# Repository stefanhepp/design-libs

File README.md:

README
------

Collection of design files and templates for 3D modelling and PCB design.

- `boards`: Contains various PCB boards and schematics
- `kicad`: KiCAD symbols, footprints and templates (for design rules)

KiCAD Libraries
---------------

### Symbols

The `kicad/symbols` folder contains the following symbol libraries:
- `Custom_Symbols`: A library of various schematic symbols.
    - `R_Pack04_SIL`: A copy of the KiCAD `R_Pack04` symbol, but using throughhole SIL package footprint and pin numbering, since the standard KiCAD SIL symbols use too much space.
    - `Mini-DIN-2x6`: Two mini-DIN 6pin units in one symbol, to use with a dual-miniDIN-6 socket
- `Custom_MCU_Module': A library of MCU devkit symbols.
    - `ESP32-DevKitC_fixed`: A copy of the Expressif ESP32 38pin devkit symbol, but using alternative footprints.
    - `ESP32-WROOM32-Devkit`: Symbol for the 30pin ESP32 dev boards.

### Footprints and 3D Models

The `kicad/footprints` folder contains the following footprint libraries:
- `Custom_Heatsinks.pretty`: A footprint library for various heatsinks.
    - `Heatsink_Aavid_TO-220_H12.7mm`: Simple TO220 heatsink
- `Custom_Connectors.pretty`: A footprint library for various connectors.
- `Custom_Module.pretty`: A footprint library for various MCU devkit modules.

The `kicad/3dmodels` folder contains the following 3D models, used with the footprints:
- `Custom_Connectors.3dmodels`: 3D models of connectors
    - `DIN5 PCB DELTRON`: DIN-5 PCB Socket, model from https://grabcad.com/library/din5-pcb-socket-90

### Board Templates

The `kicad/templates` folder contains PCB setting templates:
- Single-sided PCB, 0.3mm track width (fine tracks, allows routing between pins)
- Single-sided PCB, 0.4mm track width (coarse tracks, easy to mill)
- Double-sided PCB, 0.3mm track width (fine tracks, allows routing between pins)
- Double-sided PCB, 0.4mm track width (coarse tracks, easy to mill)

Additional Libraries, ...
-------------------------

### KiCAD Libraries

- Teensy Symbols, footprints, 3D models
    - https://github.com/XenGi/teensy_library
    - https://github.com/XenGi/teensy.pretty
- Arduino Symbols, footprints, 3D models
    - https://github.com/g200kg/kicad-lib-arduino.git

### Board Templates

- Aisler PCB template:
- PCBWay PCB template:

License
-------
Shield: [![CC BY-SA 4.0][cc-by-sa-shield]][cc-by-sa]

This work is licensed under a
[Creative Commons Attribution-ShareAlike 4.0 International License][cc-by-sa].

[![CC BY-SA 4.0][cc-by-sa-image]][cc-by-sa]

[cc-by-sa]: http://creativecommons.org/licenses/by-sa/4.0/
[cc-by-sa-image]: https://licensebuttons.net/l/by-sa/4.0/88x31.png
[cc-by-sa-shield]: https://img.shields.io/badge/License-CC%20BY--SA%204.0-lightgrey.svg

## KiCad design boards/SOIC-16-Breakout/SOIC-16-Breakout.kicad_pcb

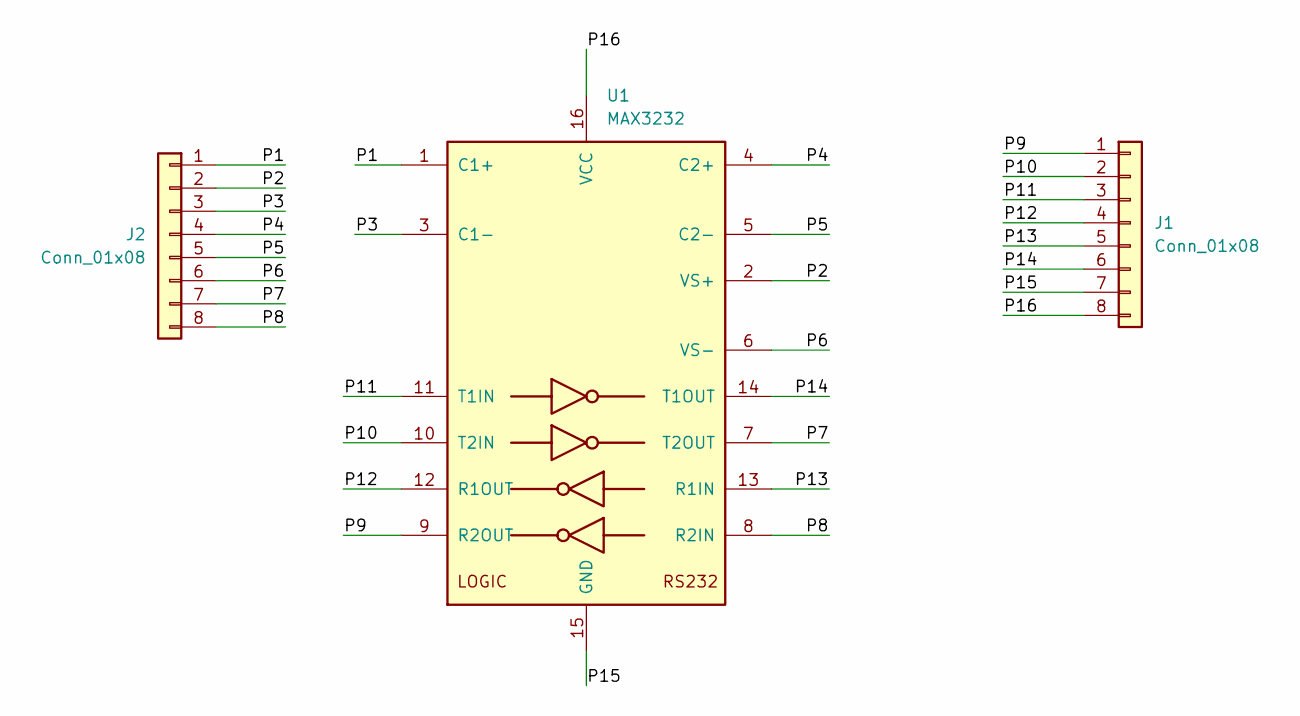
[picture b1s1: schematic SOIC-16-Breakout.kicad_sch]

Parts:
J1, J2: Conn_01x08; PinHeader_1x08_P2.54mm_Vertical
U1: MAX3232; SOIC-16_3.9x9.9mm_P1.27mm

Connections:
/P1: J2.1, U1.1 (C1+)
/P2: J2.2, U1.2 (VS+)
/P3: J2.3, U1.3 (C1-)
/P4: J2.4, U1.4 (C2+)
/P5: J2.5, U1.5 (C2-)
/P6: J2.6, U1.6 (VS-)
/P7: J2.7, U1.7 (T2OUT)
/P8: J2.8, U1.8 (R2IN)
/P9: J1.1, U1.9 (R2OUT)
/P10: J1.2, U1.10 (T2IN)
/P11: J1.3, U1.11 (T1IN)
/P12: J1.4, U1.12 (R1OUT)
/P13: J1.5, U1.13 (R1IN)
/P14: J1.6, U1.14 (T1OUT)
/P15: J1.7, U1.15 (GND)
/P16: J1.8, U1.16 (VCC)

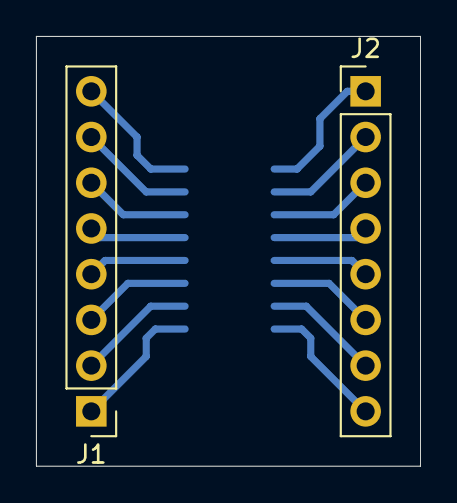
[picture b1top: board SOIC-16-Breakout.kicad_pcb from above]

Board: 2 copper layers, 21.3 x 23.9 mm, 3 parts (1 on the bottom side), 16 nets.

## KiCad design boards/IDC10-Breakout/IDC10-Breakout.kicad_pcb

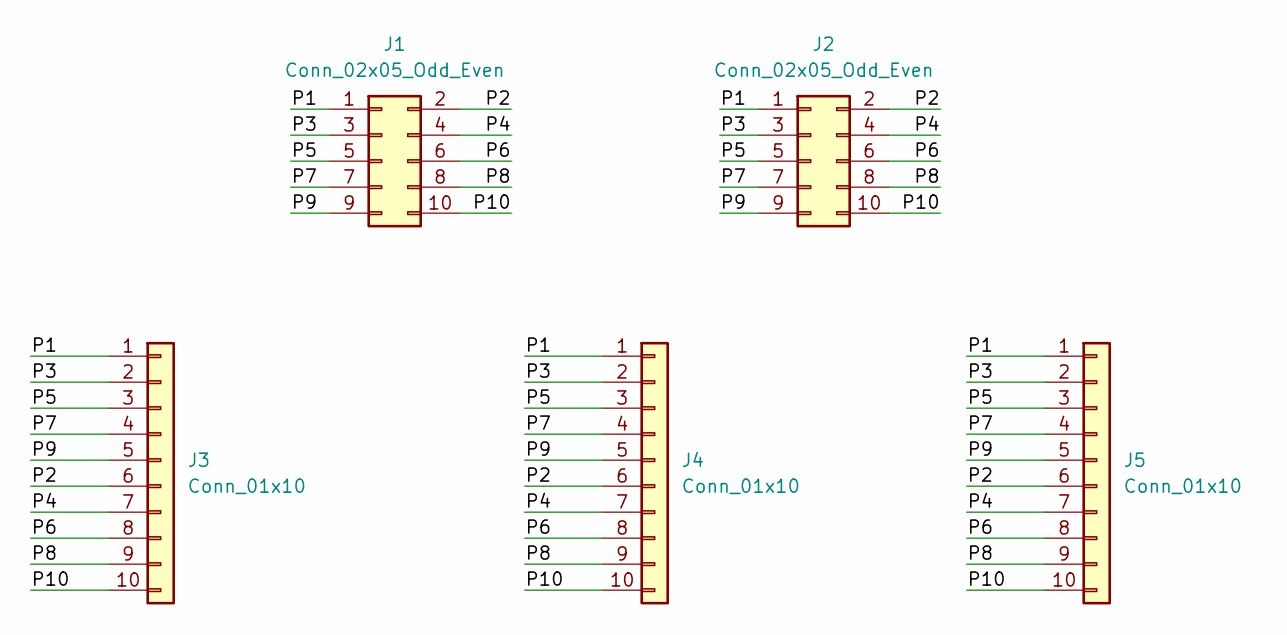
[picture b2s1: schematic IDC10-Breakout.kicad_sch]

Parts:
J1, J2: Conn_02x05_Odd_Even; IDC-Header_2x05_P2.54mm_Vertical
J3: Conn_01x10; PinHeader_1x10_P2.54mm_Vertical
J4, J5: Conn_01x10; PinSocket_1x10_P2.54mm_Vertical

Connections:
/P1: J1.1, J2.1, J3.1, J4.1, J5.1
/P2: J1.2, J2.2, J3.6, J4.6, J5.6
/P3: J1.3, J2.3, J3.2, J4.2, J5.2
/P4: J1.4, J2.4, J3.7, J4.7, J5.7
/P5: J1.5, J2.5, J3.3, J4.3, J5.3
/P6: J1.6, J2.6, J3.8, J4.8, J5.8
/P7: J1.7, J2.7, J3.4, J4.4, J5.4
/P8: J1.8, J2.8, J3.9, J4.9, J5.9
/P9: J1.9, J2.9, J3.5, J4.5, J5.5
/P10: J1.10, J2.10, J3.10, J4.10, J5.10

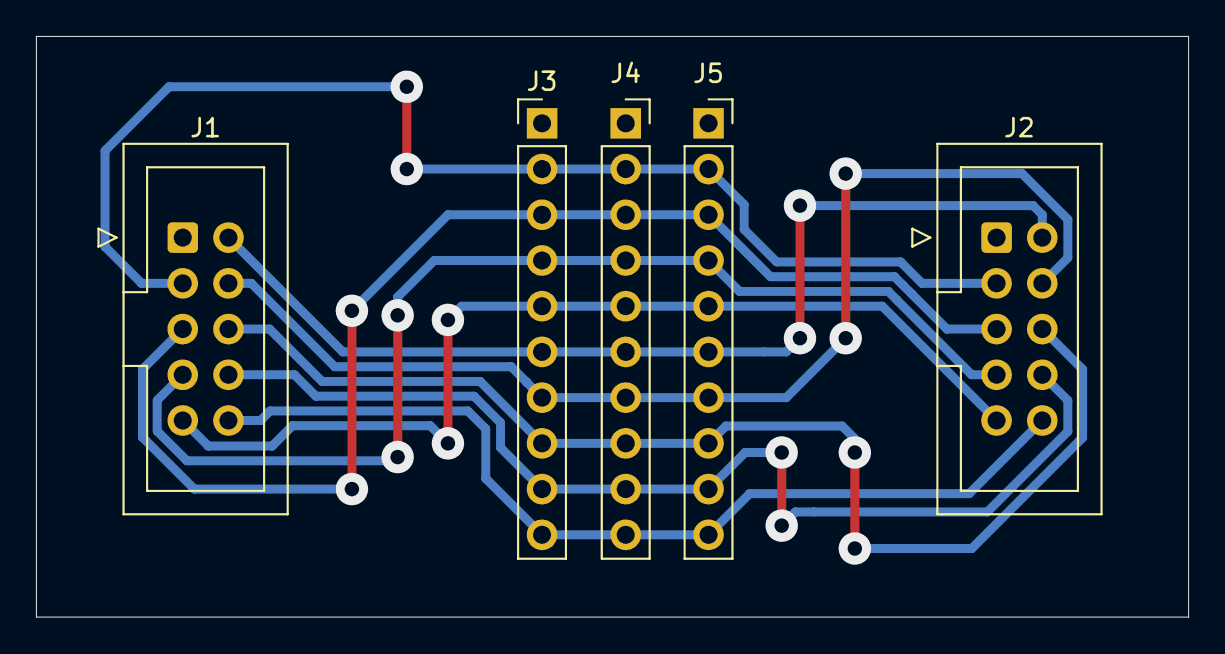
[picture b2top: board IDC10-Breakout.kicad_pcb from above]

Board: 2 copper layers, 64.0 x 32.3 mm, 5 parts (0 on the bottom side), 10 nets.

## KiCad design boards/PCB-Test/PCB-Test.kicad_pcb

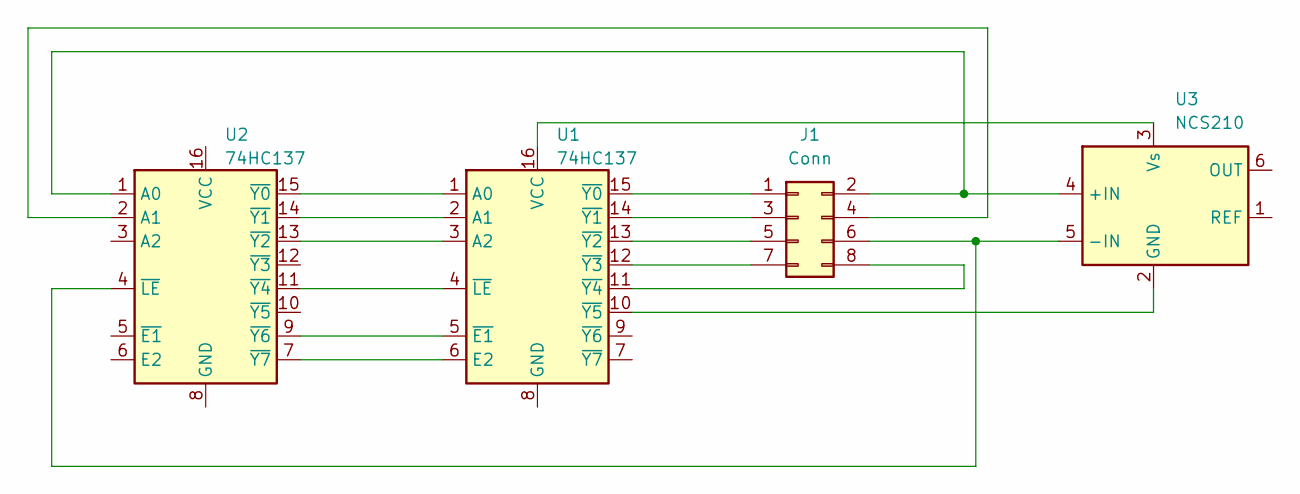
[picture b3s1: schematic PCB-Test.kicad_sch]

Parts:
J1: Conn; PinSocket_2x04_P2.54mm_Vertical
U1: 74HC137; SOIC-16_3.9x9.9mm_P1.27mm
U2: 74HC137; DIP-16_W7.62mm
U3: NCS210; SOT-363_SC-70-6_Handsoldering

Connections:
unnamed: J1.1, U1.15 (~Y0)
unnamed: J1.2, U2.1 (A0), U3.4 (+IN)
unnamed: J1.3, U1.14 (~Y1)
unnamed: J1.4, U2.2 (A1)
unnamed: J1.5, U1.13 (~Y2)
unnamed: J1.6, U2.4 (~LE), U3.5 (-IN)
unnamed: J1.7, U1.12 (~Y3)
unnamed: J1.8, U1.11 (~Y4)
unnamed: U1.1 (A0), U2.15 (~Y0)
unnamed: U1.2 (A1), U2.14 (~Y1)
unnamed: U1.3 (A2), U2.13 (~Y2)
unnamed: U1.6 (E2), U2.7 (~Y7)
unnamed: U1.16 (VCC), U3.3 (Vs)
unnamed: U1.5 (~E1), U2.9 (~Y6)
unnamed: U1.4 (~LE), U2.11 (~Y4)
unnamed: U1.10 (~Y5), U3.2 (GND)

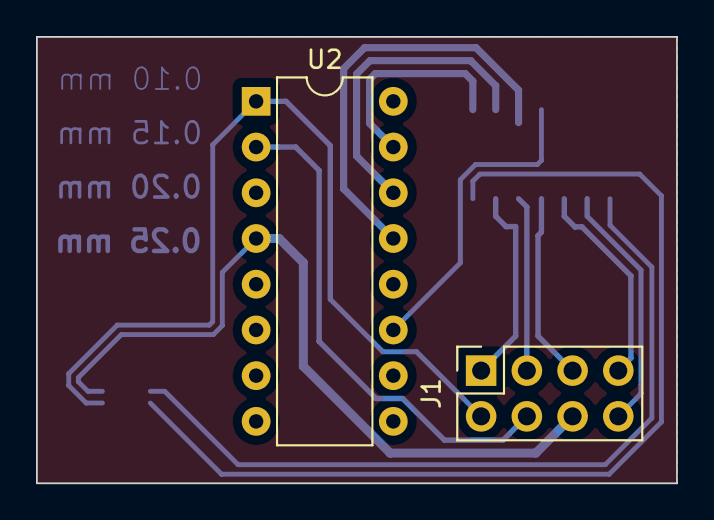
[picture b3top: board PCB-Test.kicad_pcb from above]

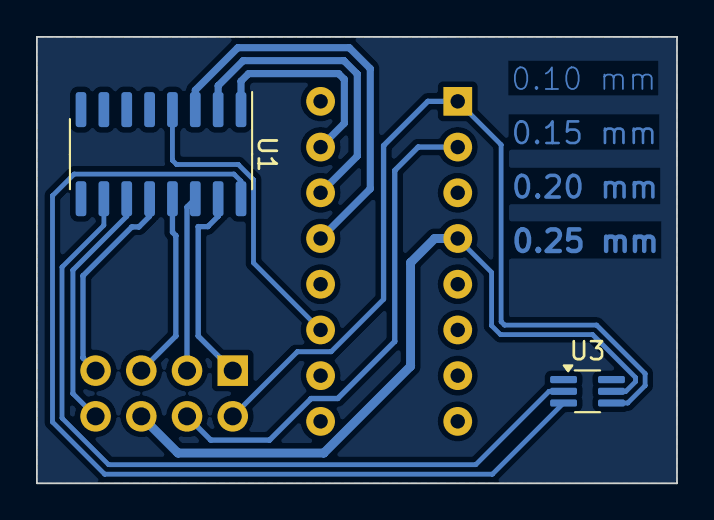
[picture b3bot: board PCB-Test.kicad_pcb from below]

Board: 2 copper layers, 35.6 x 24.8 mm, 4 parts (2 on the bottom side), 16 nets.

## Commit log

2023-04-17 Initial commit of test PCB
2023-04-18 Added KiCAD template for PCB milling design rules
2023-04-19 Updated initial gitignore and readme file
2023-05-13 Ignore object binaries
2023-06-24 Added reference to Arduino library
2023-10-21 Ignore KiCAD *.lck files
2024-03-04 Added more compact resistor pack SIL symbol
2024-03-05 Added DIN 5 footprint and model, rearranged lib folders
2024-03-06 Avoid overlap in DIN-5 connector footprint
2024-03-07 Added DCDC Gaptec converter symbol and footprint
2024-03-08 Fixed footprint size of Gaptec DCDC converter
2024-03-11 Added LTC4311 symbol
2024-03-11 Added footprint for CR2032 holder
2024-04-13 Update PCB test board with different track sizes
2024-04-14 Updated test PCB for milling, remove too small footprint
2024-05-01 Added new PCB design rule templates for PCB milling
2024-05-05 Added FlatCam tool database, updated 0.4mm PCB template settings
2024-05-06 Updated Flatcam tools db and preferences settings
2024-05-12 Updated FlatCAM endmill parameters
2024-05-18 Updated design rules for 0.32mm PCB routing
2024-06-26 Added small test PCB for tuning milling parameters, updated tools database
2024-07-27 Added IDC-10 breakout board
2024-08-04 Export gerber using milling origin
2024-09-07 Updated FlatCam tools database, IDC10 breakout board
2024-09-07 Fabrication output for IDC10 board
2024-09-07 Added FlatCAM windows start script
2024-10-20 Added audio connector footprint with pin names mapped to KiCAD symbols, and audio breakout board
2024-10-23 Updated FlatCam settings
2024-10-24 Updated FlatCam tools to use proper Preprocessor defaults and enable fast plunging
2024-10-30 Added FreeCAD CAM tool library
2024-11-03 Updated FlatCAM tools db to increase stepdown and feed speeds
2025-04-10 Added initial version of ESP32 module footprints
2025-04-10 Added new libraries to Readme
2025-04-22 Footprint for ESP32 30pin devkit module
2025-04-23 Added TO-92 footprints with larger annuals for milling
2025-05-08 Added TO-92 footprints with wider spacing for milling
2025-05-23 Added SO-16 adapter board
2025-05-26 Setup gerber output for SOIC-16 adapter
